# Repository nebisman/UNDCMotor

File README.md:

# DCmotorSystem_IoT
This is the control of a DC motor through IoT

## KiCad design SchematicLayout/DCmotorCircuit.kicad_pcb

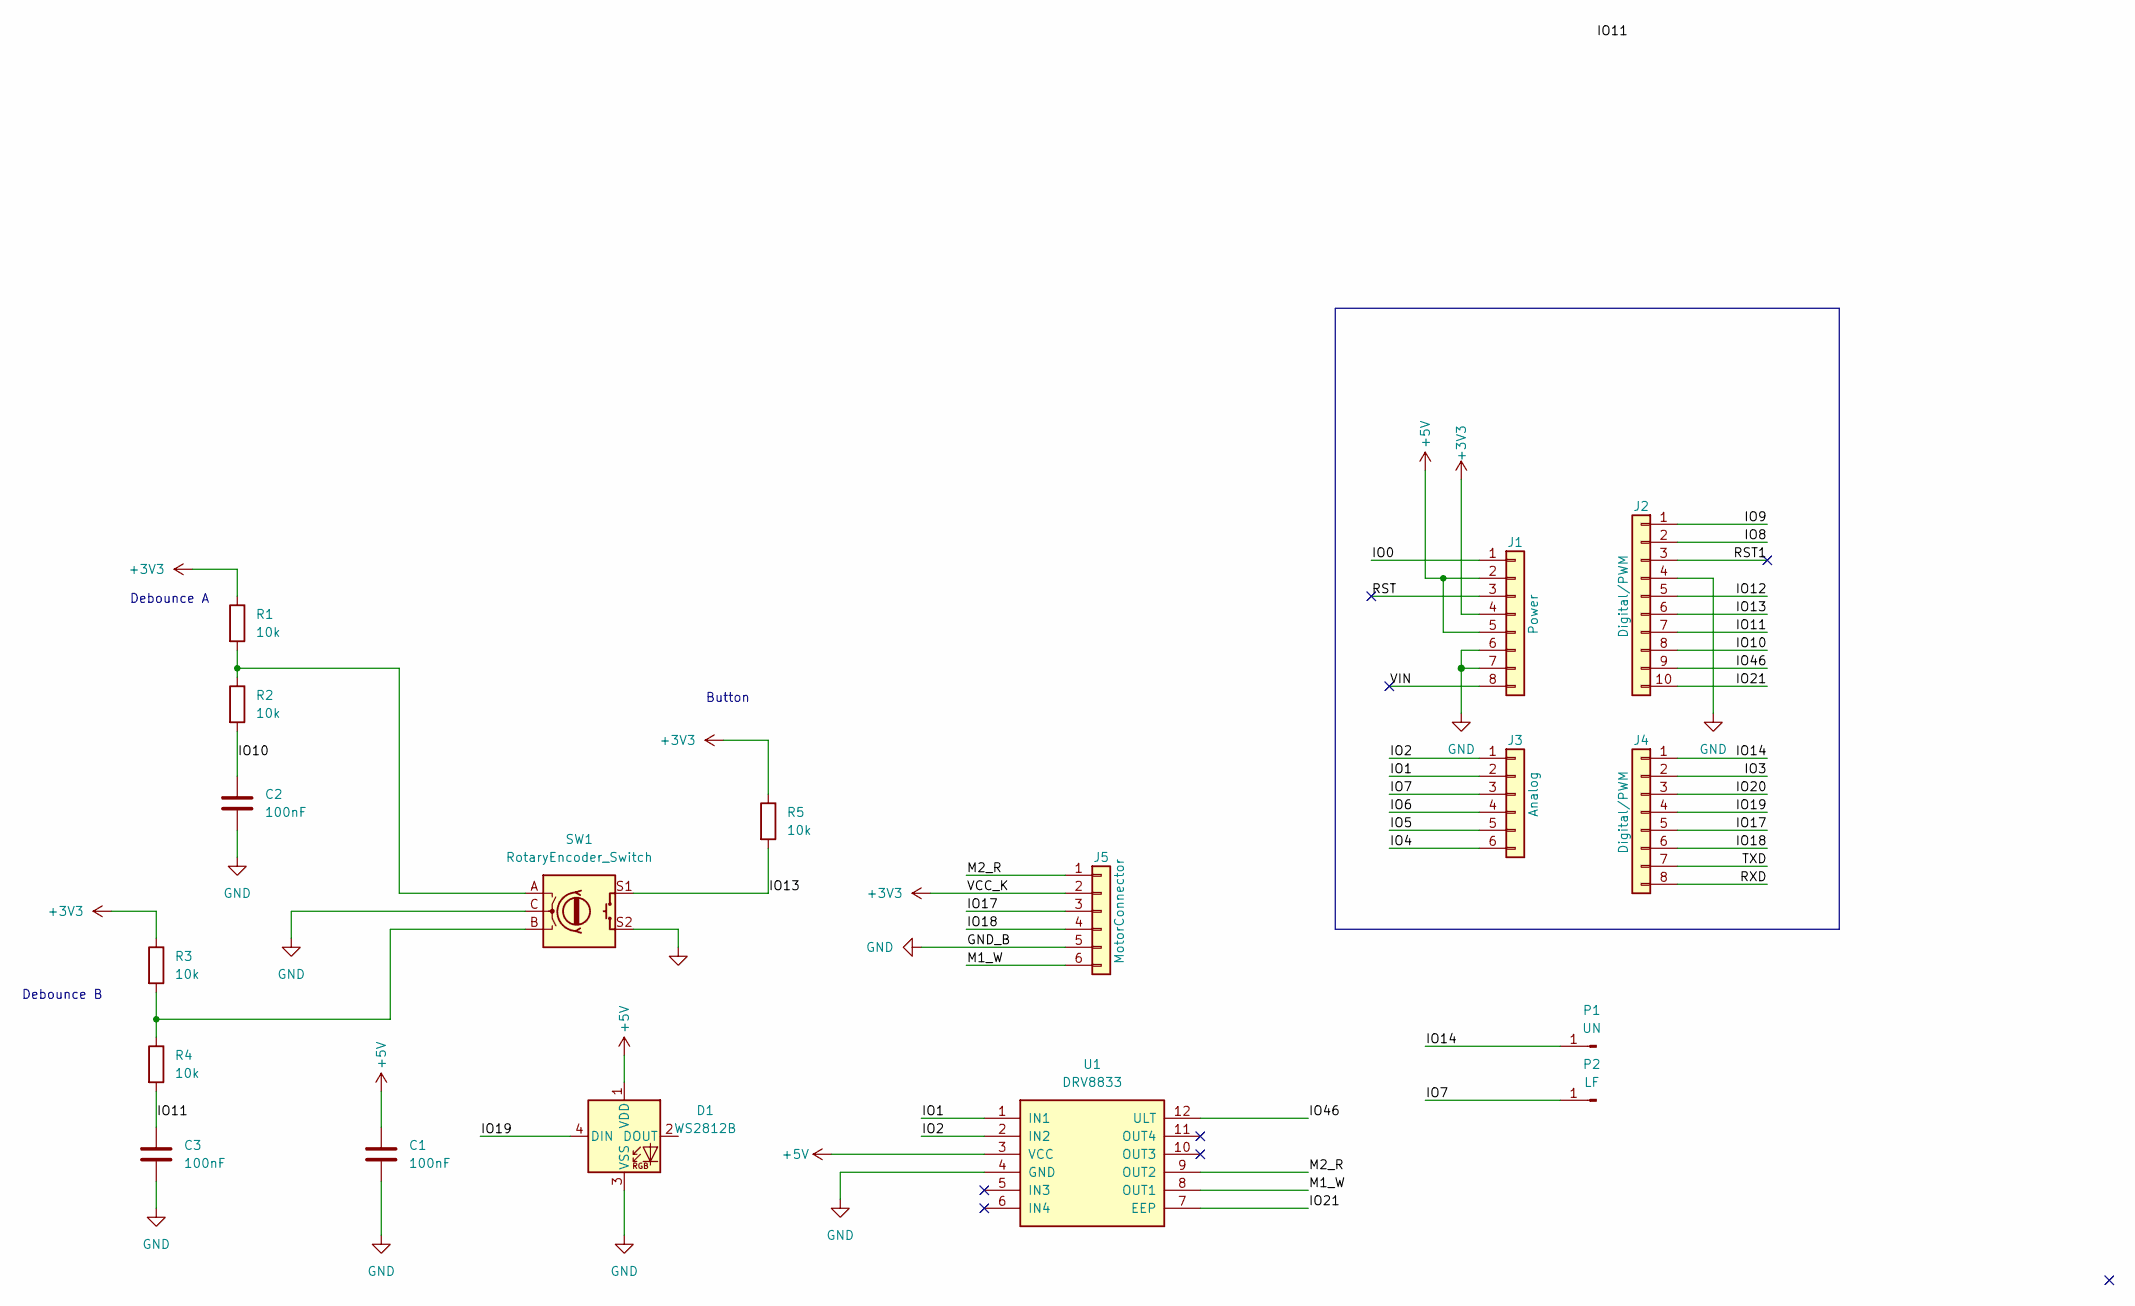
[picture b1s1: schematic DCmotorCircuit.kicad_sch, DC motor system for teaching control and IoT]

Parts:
C1, C2, C3: 100nF; C_0805_2012Metric_Pad1.18x1.45mm_HandSolder
D1: WS2812B; LED_SK6812MINI_PLCC4_3.5x3.5mm_P1.75mm
J1: Power; PinSocket_1x08_P2.54mm_Vertical
J2: Digital/PWM; PinSocket_1x10_P2.54mm_Vertical
J3: Analog; PinSocket_1x06_P2.54mm_Vertical
J4: Digital/PWM; PinSocket_1x08_P2.54mm_Vertical
J5: MotorConnector; JST_PH_B6B-PH-K_1x06_P2.00mm_Vertical
P1: UN; MountingHole_5mm_Pad_TopOnly
P2: LF; MountingHole_5mm_Pad_TopOnly
R1, R2, R3, R4, R5: 10k; R_0805_2012Metric_Pad1.20x1.40mm_HandSolder
SW1: RotaryEncoder_Switch; RotaryEncoder_Alps_EC11E-Switch_Vertical_H20mm
U1: DRV8833; drv8833module

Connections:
+3V3: J1.4, J5.2, R1.1, R3.1, R5.1
+5V: C1.1, D1.1 (VDD), J1.2, J1.5, U1.3 (VCC)
/IO0: J1.1
/IO1: J3.2, U1.1 (IN1)
/IO2: J3.1, U1.2 (IN2)
/IO3: J4.2
/IO4: J3.6
/IO5: J3.5
/IO6: J3.4
/IO7: J3.3, P2.1
/IO8: J2.2
/IO9: J2.1
/IO10: C2.1, J2.8, R2.2
/IO11: C3.1, J2.7, R4.2
/IO12: J2.5
/IO13: J2.6, R5.2, SW1.S1
/IO14: J4.1, P1.1
/IO17: J4.5, J5.3
/IO18: J4.6, J5.4
/IO19: D1.4 (DIN), J4.4
/IO20: J4.3
/IO21: J2.10, U1.7 (EEP)
/IO46: J2.9, U1.12 (ULT)
/M1_W: J5.6, U1.8 (OUT1)
/M2_R: J5.1, U1.9 (OUT2)
/RST: J1.3
/RST1: J2.3
/RXD: J4.8
/TXD: J4.7
/VIN: J1.8
GND: C1.2, C2.2, C3.2, D1.3 (VSS), J1.6, J1.7, J2.4, J5.5, SW1.C, SW1.S2, U1.4 (GND)
unnamed: R1.2, R2.1, SW1.A
unnamed: R3.2, R4.1, SW1.B

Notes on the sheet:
Debounce A
Button
Debounce B

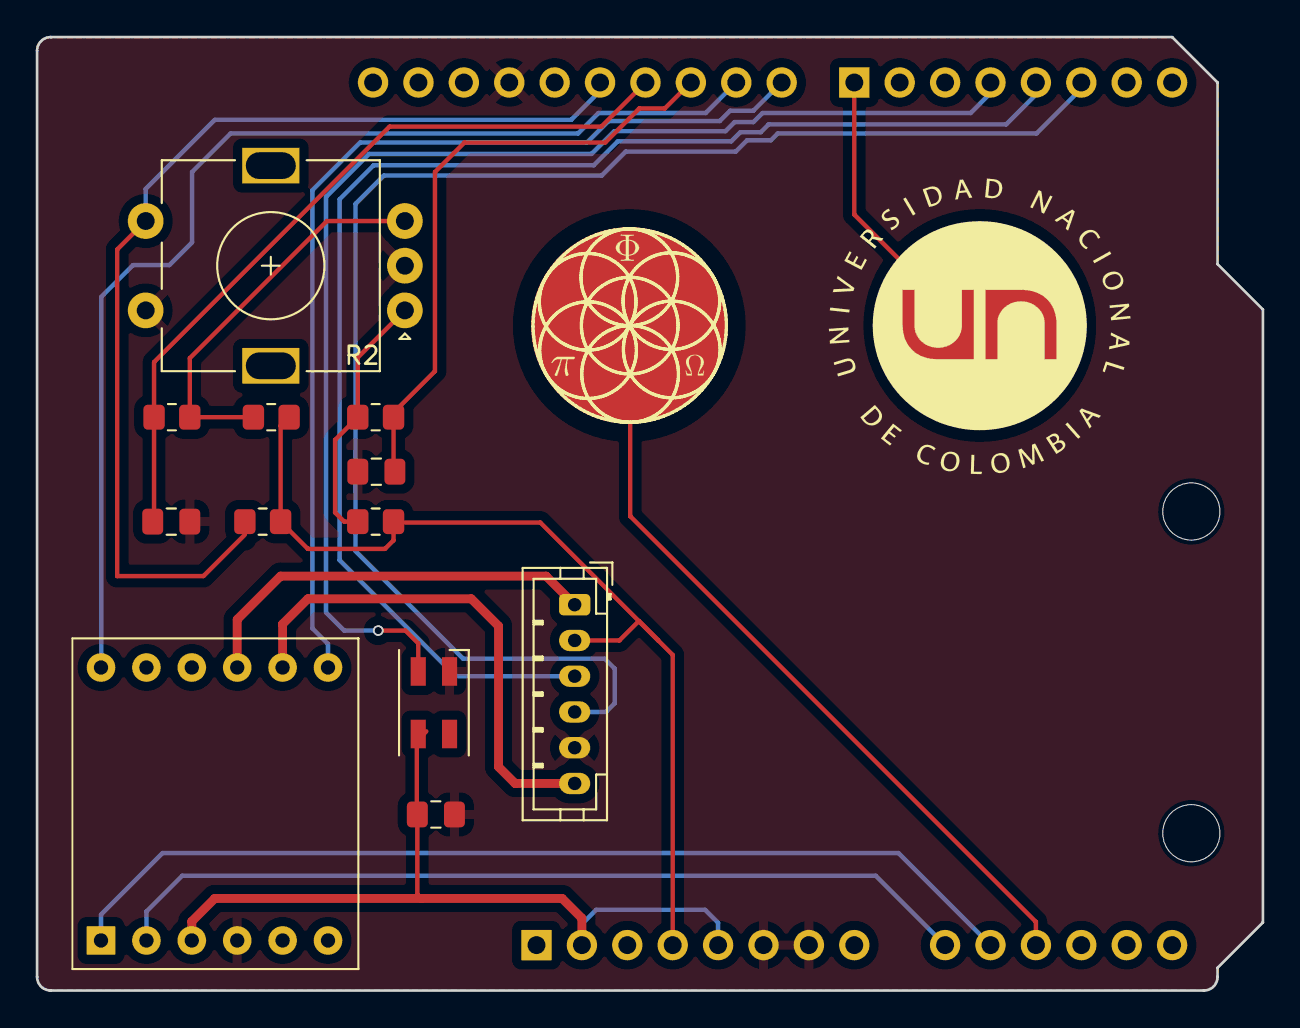
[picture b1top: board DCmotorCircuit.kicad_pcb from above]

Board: 2 copper layers, 68.6 x 53.3 mm, 20 parts (0 on the bottom side), 19 nets.

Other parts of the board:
REF1, REF2: MountingHole_3.2mm

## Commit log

2024-01-26 function to convert array to string for sending through mqtt is working
2024-01-26 last version of arduinojson included
2024-01-30 step_closed function finished
2024-02-01 function general controller has been finished
2024-02-01 the sample 0 of output has been corrected
2024-02-15 function step_open, pbrs and profile fully tested
2024-02-27 function profile and pbrs finished
2024-04-09 fir filter has been eliminated
2024-04-19 PCB files included
2024-04-19 project updated to main
2024-04-25 functions get_static_model get_fomodel_step both finished and tested
2024-05-07 controller tasks and functions updated. Now we use the kalman filter for antiwindup and change the controller realization
2024-05-26 Updated "set_controlles" so it can be used without using slycot
2024-05-27 function "set_controller" with controllable realization without using external packages
2024-05-27 circuit updated with analog filter for the encoder GY-40
2024-05-28 Update LICENSE
2024-05-28 Updated "set_controllers" so it can be used without using slycot
2024-05-28 function profile fully tested
2024-05-28 identification functions fully tested
2024-08-03 updating basic files for packaging
2024-08-03 added files for packaging
2024-08-03 completing packaging
2024-08-03 pyproject updated
2024-08-03 changing backend to widget
2024-08-03 try 2
2024-08-03 try 3
2024-08-03 manifest corrected
2024-08-05 all functions are working in jupyter
2024-08-05 added example of networks's configuration
2024-08-06 updated y scale axis for step closed
2024-08-07 step open updated to maximum values for four points method
2024-08-07 step open updated to take maximum and mean values
2024-08-07 example of connection settings included
2024-08-07 unmotor updated for connectionm inside university
2024-08-09 firmware updated to include buttons
2024-08-09 License included
2024-08-10 We include parameter sync to synchronize the frames
2024-08-10 time between fremas at sampling time
2024-08-10 closing all the figure to disable matplot lib warning
2024-08-10 fixing the communication error when multiple requests are made.
2024-08-10 printing frames
2024-08-11 printing frames and reducing qos
2024-08-11 printing frames deb
2024-08-11 solving syncronization in controlsys
2024-08-12 added notebook for identification and model of unmotor
2024-08-12 doc for step response identification included
2024-08-12 Notebook for modeling of UNDCMotor updated
2024-08-12 Notebook for modeling of UNDCMotor revised
2024-08-13 dead zone corrected
2024-08-13 correcting connection settings
2024-08-13 fixed limits in PRBS
2024-08-13 install_unmotor and detect broker added
2024-08-13 Notebook of identification updated
2024-08-13 License updated
2024-08-15 changed connection settings for LAN
2024-08-16 canvas draw not used
2024-08-16 draw ratios
2024-08-16 ratios 3 1 in step
2024-08-16 fig canvas included
2024-08-16 Notebook updated.
2024-08-19 static model corrected
2024-08-19 notebook updated for keeping figures when closing
2024-08-22 ident updated to a minimum of 50
2024-08-22 ident updated to a minimum of 100
2024-08-22 updated example experiments
2024-08-22 Data default experiments included in the voltage to speed and speed to voltage functions
2024-08-26 corrected version of connection of MQTT broker
2024-08-27 fixed error in profile closed
2024-08-28 connection settings updated
2024-08-28 notebook updated, eliminating broker cell and writing the current
2024-08-28 PI and PID notebook added
2024-08-31 PI and PID notebook updated and corrected
2024-09-04 definition of laplace "s" has been included in the notebook
2024-09-10 static model changed to default path
2024-09-10 static model changed to data path
2024-09-10 Notebook with examples for programming controllers added
2024-09-10 Notebook with examples updated
2024-09-13 Notebook for pi and pid updated and corrected
2024-09-18 Notebook for pid and pid updated
2024-09-18 Notebook pi and pid corrected
2024-10-24 functions updated for plattformio
2024-10-24 function get_fomodel_step improved
2024-10-25 broker settings updated
2024-10-25 static gain model fixed
2024-10-25 broker settings changed
2024-10-25 removed original code
2024-10-25 doc of 4 points deleted
2024-10-26 settings fixed
2024-10-26 plattformio.ini added for visual code
2024-10-31 allow only anonimous user
2024-10-31 anonymous access fixed in firmware
2024-11-03 notebook updated
2024-11-03 firmware updated
2024-11-03 notebooks updated
2024-11-08 ylim in step closed fixed
2024-11-10 axis updated in step_closed, mplcursor added to reqs
2024-11-13 fixed error in display model
2024-11-30 dead_zone comp supressed in speed control
2024-12-01 limit fxed in step closed
2024-12-01 fixed limit in step closed
2026-01-15 diagram updated
